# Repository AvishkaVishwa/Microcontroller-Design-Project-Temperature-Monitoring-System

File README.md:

# Microcontroller-Design-Project-

This project is part of the IA 2209 - Microcontroller Laboratory course. 
It involves creating a microcontroller-based temperature monitoring system with various features including temperature display, alarm, and range indication using LEDs.

## Features

- **Temperature Display**: Displays the current temperature on a 7-segment display with the ability to switch between Celsius and Fahrenheit.
- **Temperature Alarm**: An alarm system that triggers when the temperature exceeds 40°C.
- **Temperature Range Indication**: LEDs indicate different temperature ranges with varying brightness.
- **Mode Switching**: Toggle between displaying temperature (Celsius and Fahrenheit) and temperature range.

## Components
- ATmega328P Microcontroller
- MAX7219CNG Display driver
- 4-Digit 7-segment displays
- LEDs
- Push buttons
- Resistors, capacitors, and other supporting components
## Simulation on Proteus
https://github.com/user-attachments/assets/188e2a22-0e74-4096-baf8-a73c14bb029d

## Hardware Testing
https://github.com/user-attachments/assets/ba68c1e6-b078-402f-8ae6-b2f3dc63eebe

## Usage

1. **Compile and Upload Code**: Compile the provided C/C++ code and upload it to the ATmega328P microcontroller.
2. **Hardware Setup**: Connect the hardware components as per the circuit diagram provided in `hardware/circuit_diagram.png`.
3. **Operating the System**:
   - Use the increment and decrement buttons to adjust the temperature.
   - The current temperature is displayed on the 7-segment display.
   - The alarm LED blinks if the temperature exceeds 40°C and can be acknowledged with the acknowledgment button.
   - LEDs indicate the current temperature range.

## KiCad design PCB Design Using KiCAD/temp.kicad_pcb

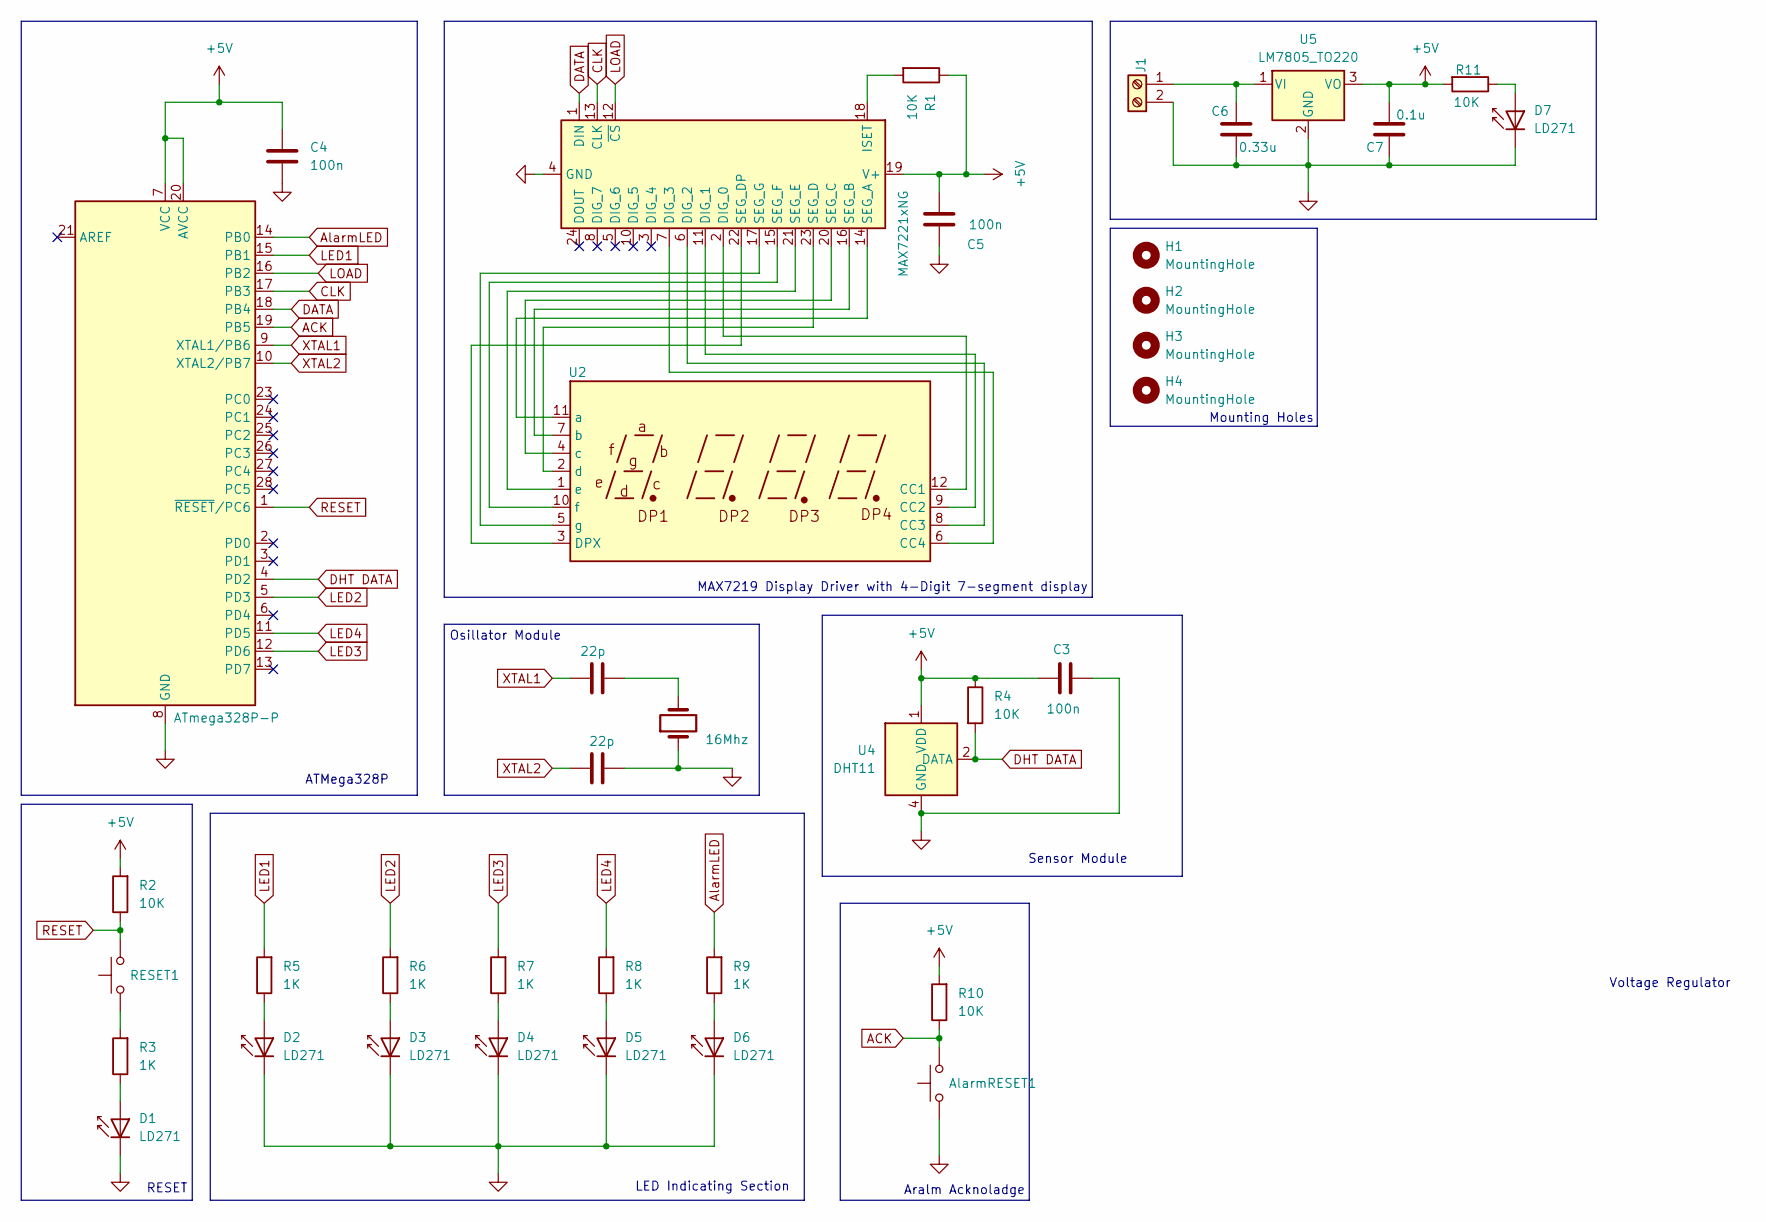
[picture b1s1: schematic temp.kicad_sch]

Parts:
16Mh1: 16Mhz; Crystal_HC52-8mm_Vertical
AlarmRESET1: SW_Push; SW_PUSH_6mm
C1, C2: 22p; C_Disc_D3.0mm_W1.6mm_P2.50mm
C3, C4: 100n; CP_Radial_D5.0mm_P2.00mm
C5: 100n; CP_Radial_D5.0mm_P2.50mm
C6: 0.33u; CP_Radial_D5.0mm_P2.00mm
C7: 0.1u; CP_Radial_D5.0mm_P2.50mm
D1, D2, D3, D4, D5, D6, D7: LD271; LED_D5.0mm_IRGrey
H1, H2, H3, H4: MountingHole; MountingHole_2.2mm_M2
J1: Screw_Terminal_01x02; TerminalBlock_Phoenix_MKDS-1,5-2-5.08_1x02_P5.08mm_Horizont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
R1, R2, R4, R10, R11: 10K; R_Axial_DIN0204_L3.6mm_D1.6mm_P5.08mm_Horizontal
R3, R5, R6, R7, R8, R9: 1K; R_Axial_DIN0204_L3.6mm_D1.6mm_P5.08mm_Horizontal
RESET1: SW_Push; SW_PUSH_6mm
U1: ATmega328P-P; DIP-28_W7.62mm
U2: CC56-12SURKWA; CA56-12SURKWA
U3: MAX7221xNG; DIP-24_W7.62mm
U4: DHT11; Aosong_DHT11_5.5x12.0_P2.54mm
U5: LM7805_TO220; TO-220-3_Vertical

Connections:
+5V: C3.2, C4.1, C5.1, C7.1, R1.1, R2.2, R4.1, R10.2, R11.2, U1.7 (VCC), U1.20 (AVCC), U3.19 (V+), U4.1 (VDD), U5.3 (VO)
ACK: AlarmRESET1.2, R10.1, U1.19 (PB5)
AlarmLED: R9.2, U1.14 (PB0)
CLK: U1.17 (PB3), U3.13 (CLK)
DATA: U1.18 (PB4), U3.1 (DIN)
DHT DATA: R4.2, U1.4 (PD2), U4.2 (DATA)
GND: 16Mh1.1, AlarmRESET1.1, C1.1, C3.1, C4.2, C5.2, C6.2, C7.2, D1.1 (K), D2.1 (K), D3.1 (K), D4.1 (K), D5.1 (K), D6.1 (K), D7.1 (K), J1.2 (Pin_1), U1.8 (GND), U1.22 (GND), U3.4 (GND), U3.9 (GND), U4.4 (GND), U5.2 (GND)
LED1: R5.2, U1.15 (PB1)
LED2: R6.2, U1.5 (PD3)
LED3: R7.2, U1.12 (PD6)
LED4: R8.2, U1.11 (PD5)
LOAD: U1.16 (PB2), U3.12 (~CS)
unnamed: 16Mh1.2, C2.2
unnamed: D1.2 (A), R3.1
unnamed: D2.2 (A), R5.1
unnamed: D3.2 (A), R6.1
unnamed: D4.2 (A), R7.1
unnamed: D5.2 (A), R8.1
unnamed: D6.2 (A), R9.1
unnamed: D7.2 (A), R11.1
unnamed: C6.1, J1.1 (Pin_2), U5.1 (VI)
unnamed: R3.2, RESET1.1
unnamed: U2.12 (CC1), U3.2 (DIG_0)
unnamed: U2.9 (CC2), U3.11 (DIG_1)
unnamed: U2.8 (CC3), U3.6 (DIG_2)
unnamed: U2.6 (CC4), U3.7 (DIG_3)
unnamed: U2.3 (DPX), U3.22 (SEG_DP)
unnamed: U2.11 (a), U3.14 (SEG_A)
unnamed: U2.7 (b), U3.16 (SEG_B)
unnamed: U2.4 (c), U3.20 (SEG_C)
unnamed: U2.2 (d), U3.23 (SEG_D)
unnamed: U2.1 (e), U3.21 (SEG_E)
unnamed: U2.10 (f), U3.15 (SEG_F)
unnamed: U2.5 (g), U3.17 (SEG_G)
unnamed: R1.2, U3.18 (ISET)
RESET: R2.1, RESET1.2, U1.1 (~RESET/PC6)
XTAL1: C2.1, U1.9 (XTAL1/PB6)
XTAL2: C1.2, U1.10 (XTAL2/PB7)

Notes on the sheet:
Aralm Acknoladge
ATMega328P
Osillator Module
MAX7219 Display Driver with 4-Digit 7-segment display
Mounting Holes
LED Indicating Section
RESET
Voltage Regulator
Sensor Module

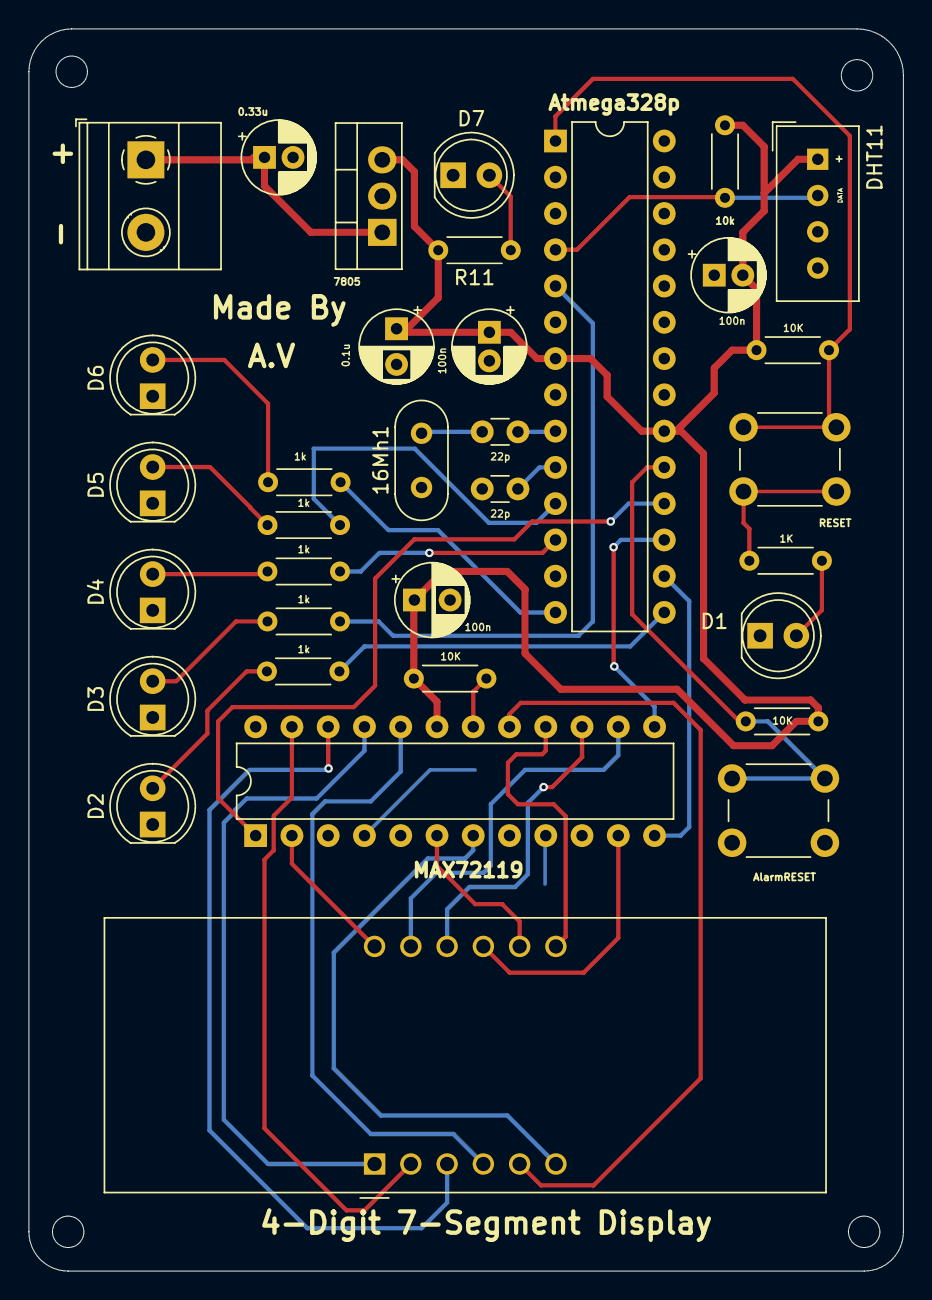
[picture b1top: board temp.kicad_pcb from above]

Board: 2 copper layers, 61.2 x 87.0 mm, 38 parts (1 on the bottom side), 38 nets.

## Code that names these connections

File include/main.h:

#ifndef MAIN_H
#define MAIN_H

#include <avr/io.h>
#include <util/delay.h>
#include <stdbool.h>
#include "spi.h"
#include "max7219.h"

// Pin connections for the push buttons and LEDs
#define INC_BUTTON PD2
#define DEC_BUTTON PD3
#define MODE_BUTTON PD4
#define ACK_BUTTON PB0  // New pin for the acknowledgment button
#define LED1 PB1
#define LED2 PD5
#define LED3 PD6
#define LED4 PD7
#define ALARM_LED PB4

// Variables for storing the state
extern int temperatureC;  // Initial temperature in Celsius
extern bool isCelsius;  // Start in Celsius mode
extern bool alarmAcknowledged;  // New variable to track alarm acknowledgment

// Debouncing variables
extern unsigned long lastDebounceTimeInc;
extern unsigned long lastDebounceTimeDec;
extern unsigned long lastDebounceTimeMode;
extern unsigned long lastDebounceTimeAck;
extern const unsigned long debounceDelay;

// Variables to keep track of button state
extern bool lastIncButtonState;
extern bool lastDecButtonState;
extern bool lastModeButtonState;
extern bool lastAckButtonState;  // New variable for acknowledgment button state

// Variables for blinking alarm LED
extern unsigned long lastBlinkTime;
extern bool alarmState;
extern const unsigned long blinkInterval;  // Blink interval in milliseconds

// Function prototypes
void updateLEDs(void);
void handleAlarmBlink(void);
void increaseTemperature(void);
void decreaseTemperature(void);
void switchMode(void);
void toggleAlarmAcknowledgment(void);
void handleButton(bool currentState, bool *lastState, unsigned long *lastDebounceTime, void (*action)());
unsigned long millis(void);
unsigned long micros(void);

#endif // MAIN_H

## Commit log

2024-06-05 Design Project 2.2
2024-06-05 hardware implementation
2024-06-05 edit
2024-06-05 edited
2024-06-29 V2.1
2024-06-29 KiCAD
2024-06-30 PCD V.3
2024-07-01 PCD v3
2024-10-18 main
2024-11-21 added some details of implementing phases
